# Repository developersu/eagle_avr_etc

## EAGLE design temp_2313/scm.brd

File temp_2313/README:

DHT11 humidity sensor on attiny2313
Software could be found somewhere in mine repos.

Distribution: GNU GPL v.3 for more information please visit https://www.gnu.org/licenses/gpl-3.0.en.html

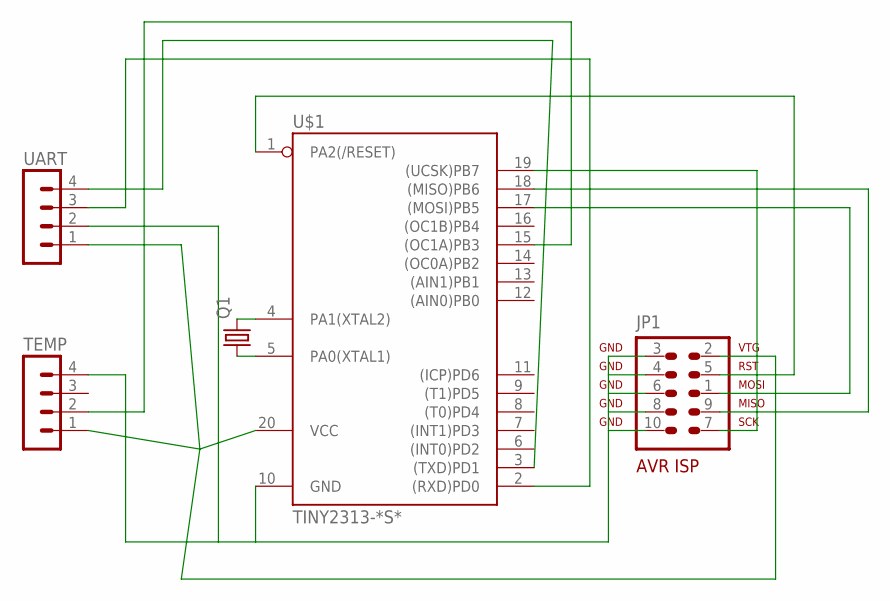
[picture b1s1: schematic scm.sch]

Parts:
JP1: AVR-ISP-10
Q1: CRYSTALHC49U70; HC49U70
TEMP: MA04-1
U$1: TINY2313-*S*; SO20L$
UART: MA04-1

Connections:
unnamed: JP1.3, JP1.4, JP1.6, JP1.8, JP1.10, TEMP.4, U$1.10 (GND), UART.2
unnamed: JP1.2, TEMP.1, U$1.20 (VCC), UART.1
unnamed: JP1.5, U$1.1 (PA2(/RESET))
unnamed: JP1.7, U$1.19 ((UCSK)PB7)
unnamed: JP1.1, U$1.17 ((MOSI)PB5)
unnamed: JP1.9, U$1.18 ((MISO)PB6)
unnamed: TEMP.2, U$1.15 ((OC1A)PB3)
unnamed: U$1.2 ((RXD)PD0), UART.3
unnamed: U$1.3 ((TXD)PD1), UART.4
unnamed: Q1.2, U$1.4 (PA1(XTAL2))
unnamed: Q1.1, U$1.5 (PA0(XTAL1))

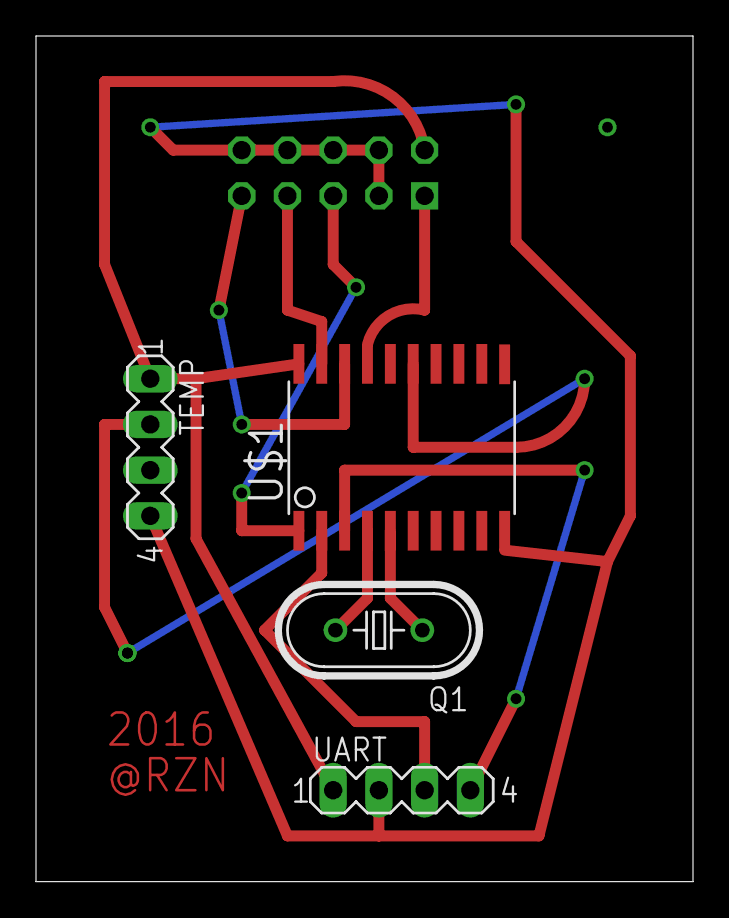
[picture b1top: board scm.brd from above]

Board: 2 copper layers, 36.5 x 47.0 mm, 5 parts (1 on the bottom side), 11 nets.

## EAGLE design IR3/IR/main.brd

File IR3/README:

IR reciever for PCB for EAGLE 7.4.0 Light
Based on 'Igorplugusb'
More information: http://developersu.blogspot.ru/2016/03/ir-lirc-igorplugusb.html

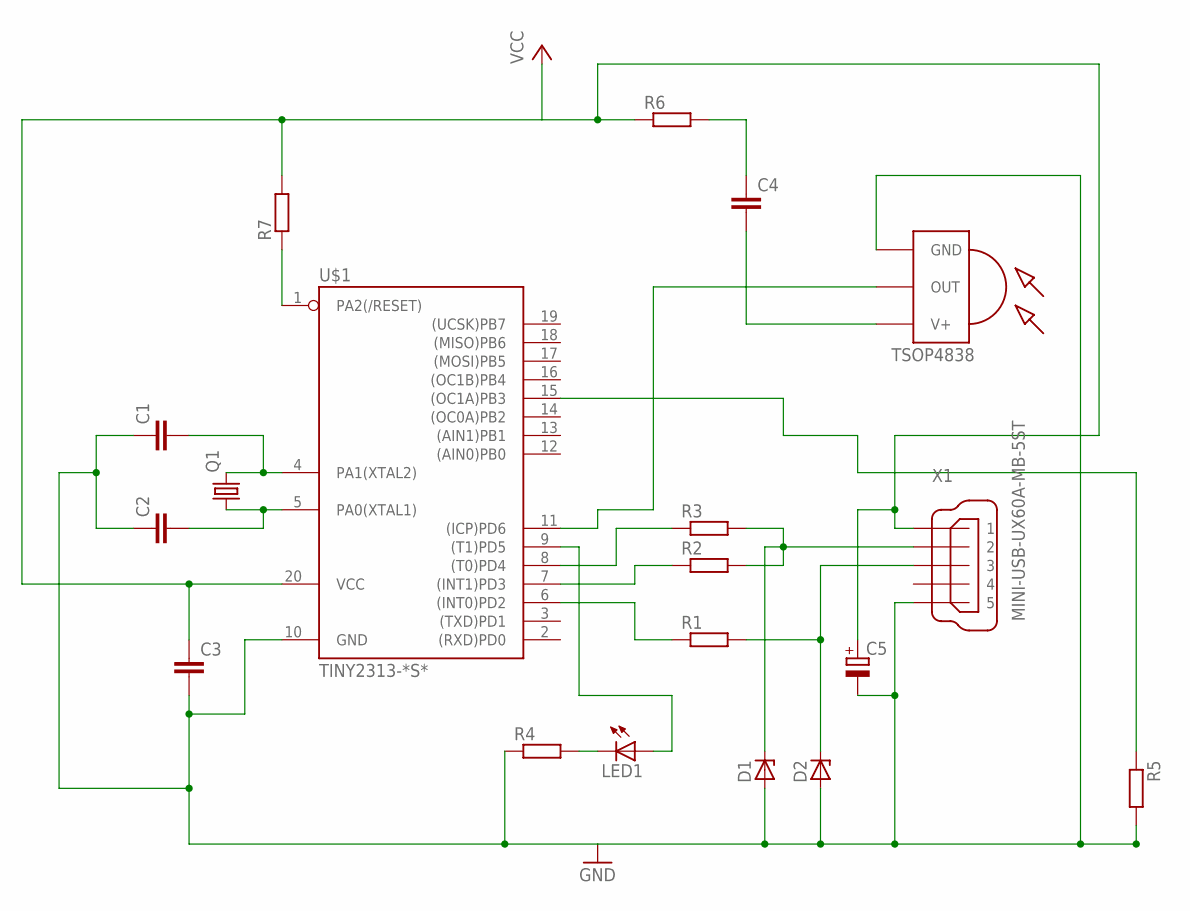
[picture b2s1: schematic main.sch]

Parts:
C1, C2, C3, C4: C-EUC0603; C0603
C5: CPOL-EUE2.5-6; E2,5-6
D1, D2: ZENER-DIODESOD80C; SOD80C
LED1: LED3MM
Q1: CRYSTALHC49U70; HC49U70
R1, R2, R3, R4, R5, R6, R7: R-EU_R0603; R0603
U$1: TINY2313-*S*; SO20L$
U$2: TSOP4838; TSOP18XX
X1: MINI-USB-UX60A-MB-5ST; UX60A-MB-5ST

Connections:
GND: C1.1, C2.1, C3.2, C5.-, D1.A, D2.A, R4.1, R5.2, U$1.10 (GND), U$2.GND, X1.5
unnamed: C1.2, Q1.2, U$1.4 (PA1(XTAL2))
unnamed: C2.2, Q1.1, U$1.5 (PA0(XTAL1))
unnamed: R7.1, U$1.1 (PA2(/RESET))
unnamed: C3.1, C5.+, R6.1, R7.2, U$1.20 (VCC), X1.1
unnamed: LED1.K (C), R4.2
unnamed: R5.1, U$1.15 ((OC1A)PB3)
unnamed: LED1.A, U$1.9 ((T1)PD5)
unnamed: R3.1, U$1.8 ((T0)PD4)
unnamed: R2.1, U$1.7 ((INT1)PD3)
unnamed: R1.1, U$1.6 ((INT0)PD2)
unnamed: C4.2, U$2.VCC (V+)
unnamed: U$1.11 ((ICP)PD6), U$2.OUT
unnamed: D1.C, R2.2, R3.2, X1.2
unnamed: D2.C, R1.2, X1.3
unnamed: C4.1, R6.2

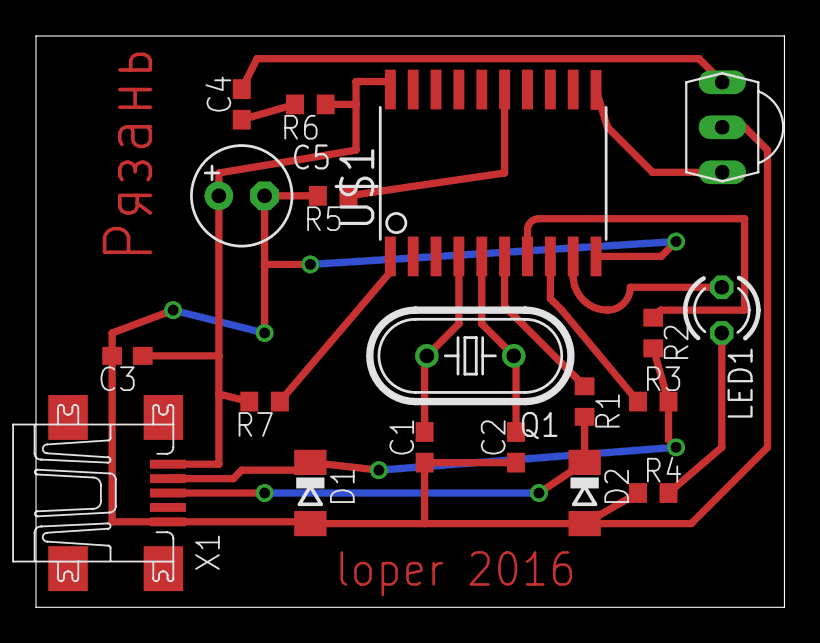
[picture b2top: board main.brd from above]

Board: 2 copper layers, 41.6 x 31.7 mm, 19 parts (0 on the bottom side), 16 nets.

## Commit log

2016-11-27 re-load
